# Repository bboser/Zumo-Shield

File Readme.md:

# Zumo Shield 

PCB shield design for the [Pololu](https://www.pololu.com) [Zumo Robot Chassis](https://www.pololu.com/product/1418) in [Eagle CAD](https://www.autodesk.com/products/eagle/overview).

Alternative to circuit boards from Pololu when you want to design your own electronics. The following features are included on the board:

* Cutouts and solder tabs for the battery
* JP1 power "switch"
* JP2 header to microcontroller
* Motor caps (smd components)
* 4 magnetic sensors (smd components)

The board has been fabricated by [OSH Park](https://oshpark.com). If you use a different PCB fab, make sure that it will cut out the "holes" for the battery tabs (VBAT+ and VBAT- on the PCB layout).

*Acknowledgement:* many thanks to Polou for providing a cad file with the locations of the holes and mag sensors of the Zumo.

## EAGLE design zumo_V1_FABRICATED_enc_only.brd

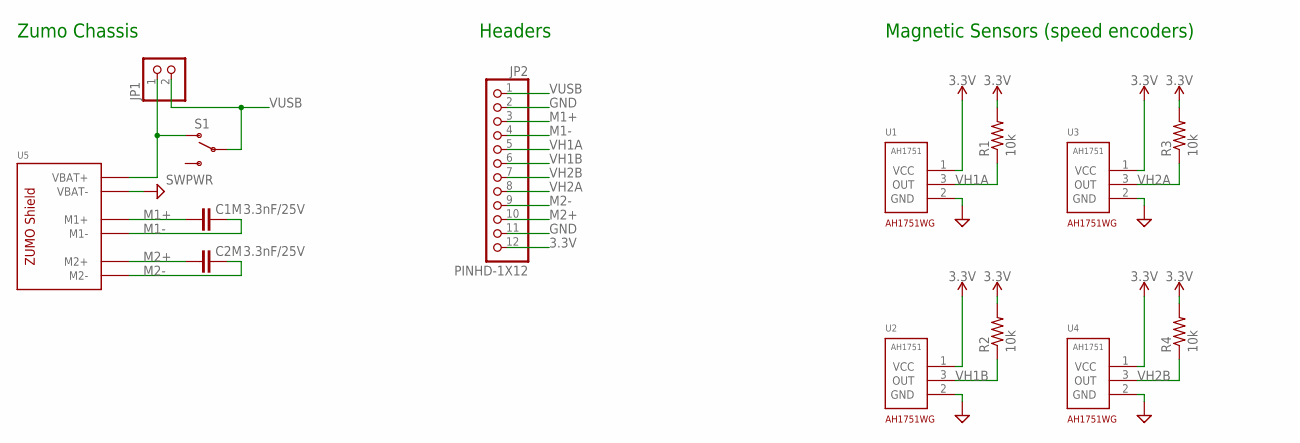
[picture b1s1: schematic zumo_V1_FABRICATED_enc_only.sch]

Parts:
C1M, C2M: 3.3nF/25V; C0805; DIGIKEY 732-8052-6-ND
JP1: JPWR; 1X02
JP2: PINHD-1X12; 1X12
R1, R2, R3, R4: 10k; R0805
S1: SWPWR; AYZ0202; DIGIKEY 401-2013-6-ND
U1, U2, U3, U4: AH1751WG; SC59
U5: ZUMONO_TABS; ZUMO_NO_TABS

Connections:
3.3V: JP2.12, R1.2, R2.2, R3.2, R4.2, U1.1 (VCC), U2.1 (VCC), U3.1 (VCC), U4.1 (VCC)
GND: JP2.2, JP2.11, U1.2 (GND), U2.2 (GND), U3.2 (GND), U4.2 (GND), U5.VBAT-
M1+: C1M.2, JP2.3, U5.M1+
M1-: C1M.1, JP2.4, U5.M1-
M2+: C2M.2, JP2.10, U5.M2+
M2-: C2M.1, JP2.9, U5.M2-
VBAT: JP1.1, S1.1 (O), U5.VBAT+
VH1A: JP2.5, R1.1, U1.3 (OUT)
VH1B: JP2.6, R2.1, U2.3 (OUT)
VH2A: JP2.8, R3.1, U3.3 (OUT)
VH2B: JP2.7, R4.1, U4.3 (OUT)
VUSB: JP1.2, JP2.1, S1.2

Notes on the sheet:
Zumo Chassis
Magnetic Sensors (speed encoders)
Headers

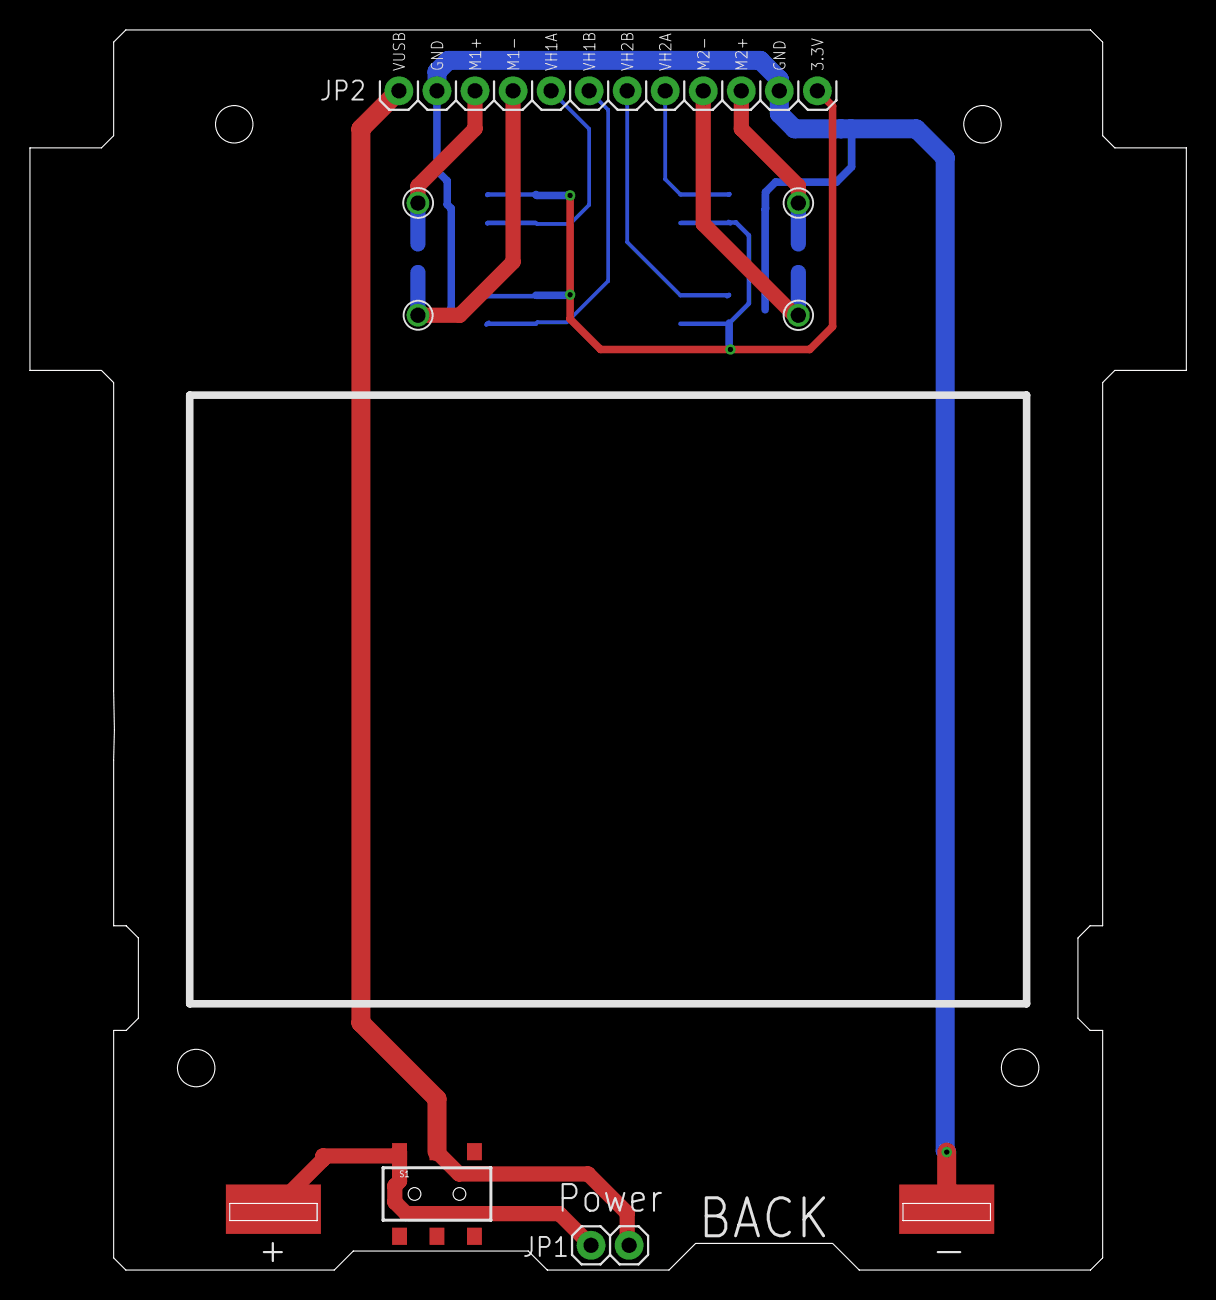
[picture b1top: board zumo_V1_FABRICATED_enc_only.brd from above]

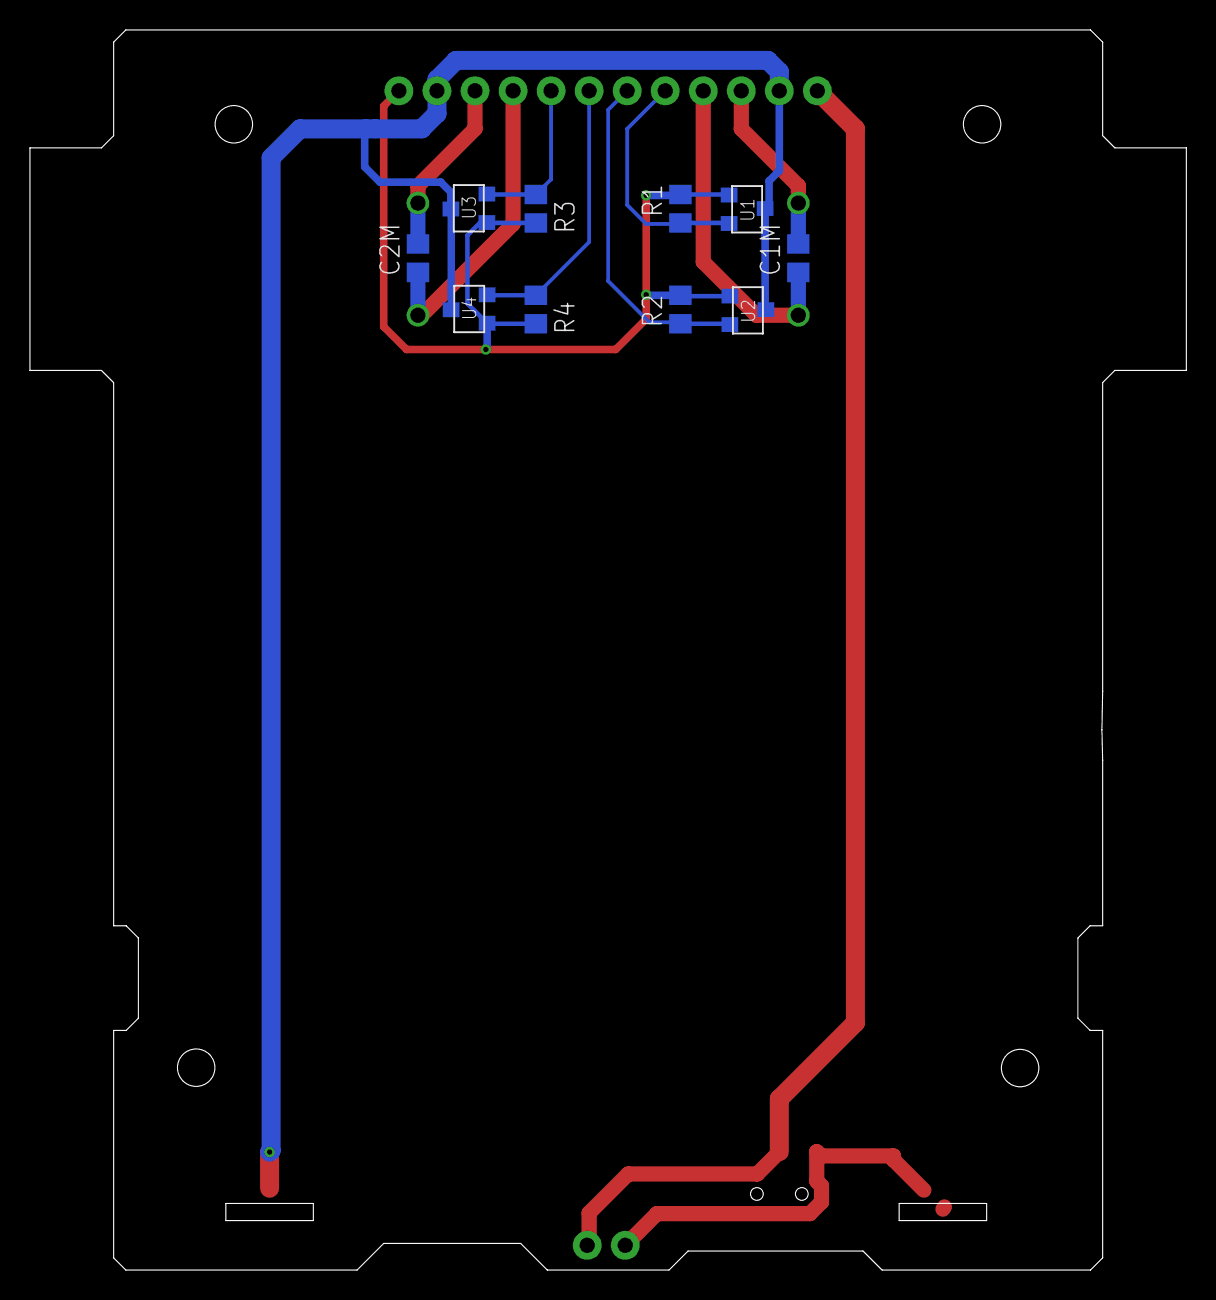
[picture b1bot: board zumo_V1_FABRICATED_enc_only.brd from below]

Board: 2 copper layers, 77.2 x 82.8 mm, 14 parts (10 on the bottom side), 12 nets.

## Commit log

2017-12-01 initial
2017-12-01 typo

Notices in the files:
parts and their libraries:
SparkFun: Licensing: CC v3.0 Share-Alike You are welcome to use this library for commercial purposes.
